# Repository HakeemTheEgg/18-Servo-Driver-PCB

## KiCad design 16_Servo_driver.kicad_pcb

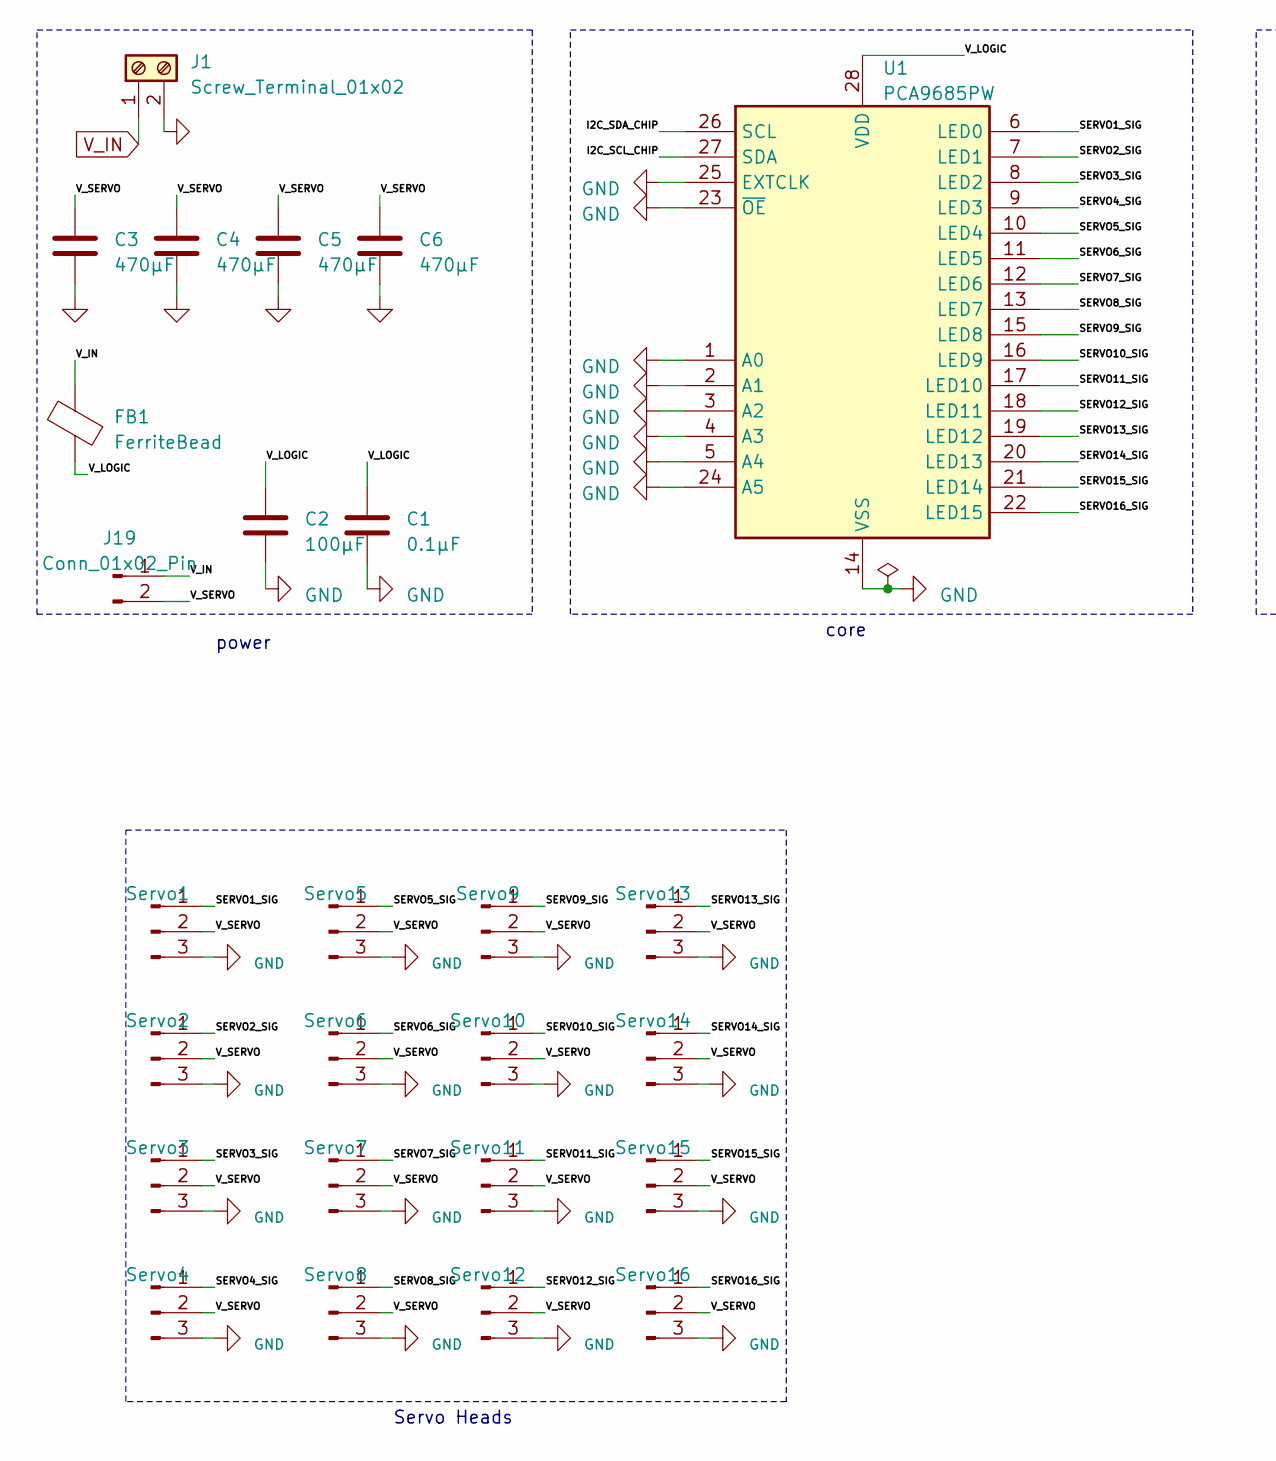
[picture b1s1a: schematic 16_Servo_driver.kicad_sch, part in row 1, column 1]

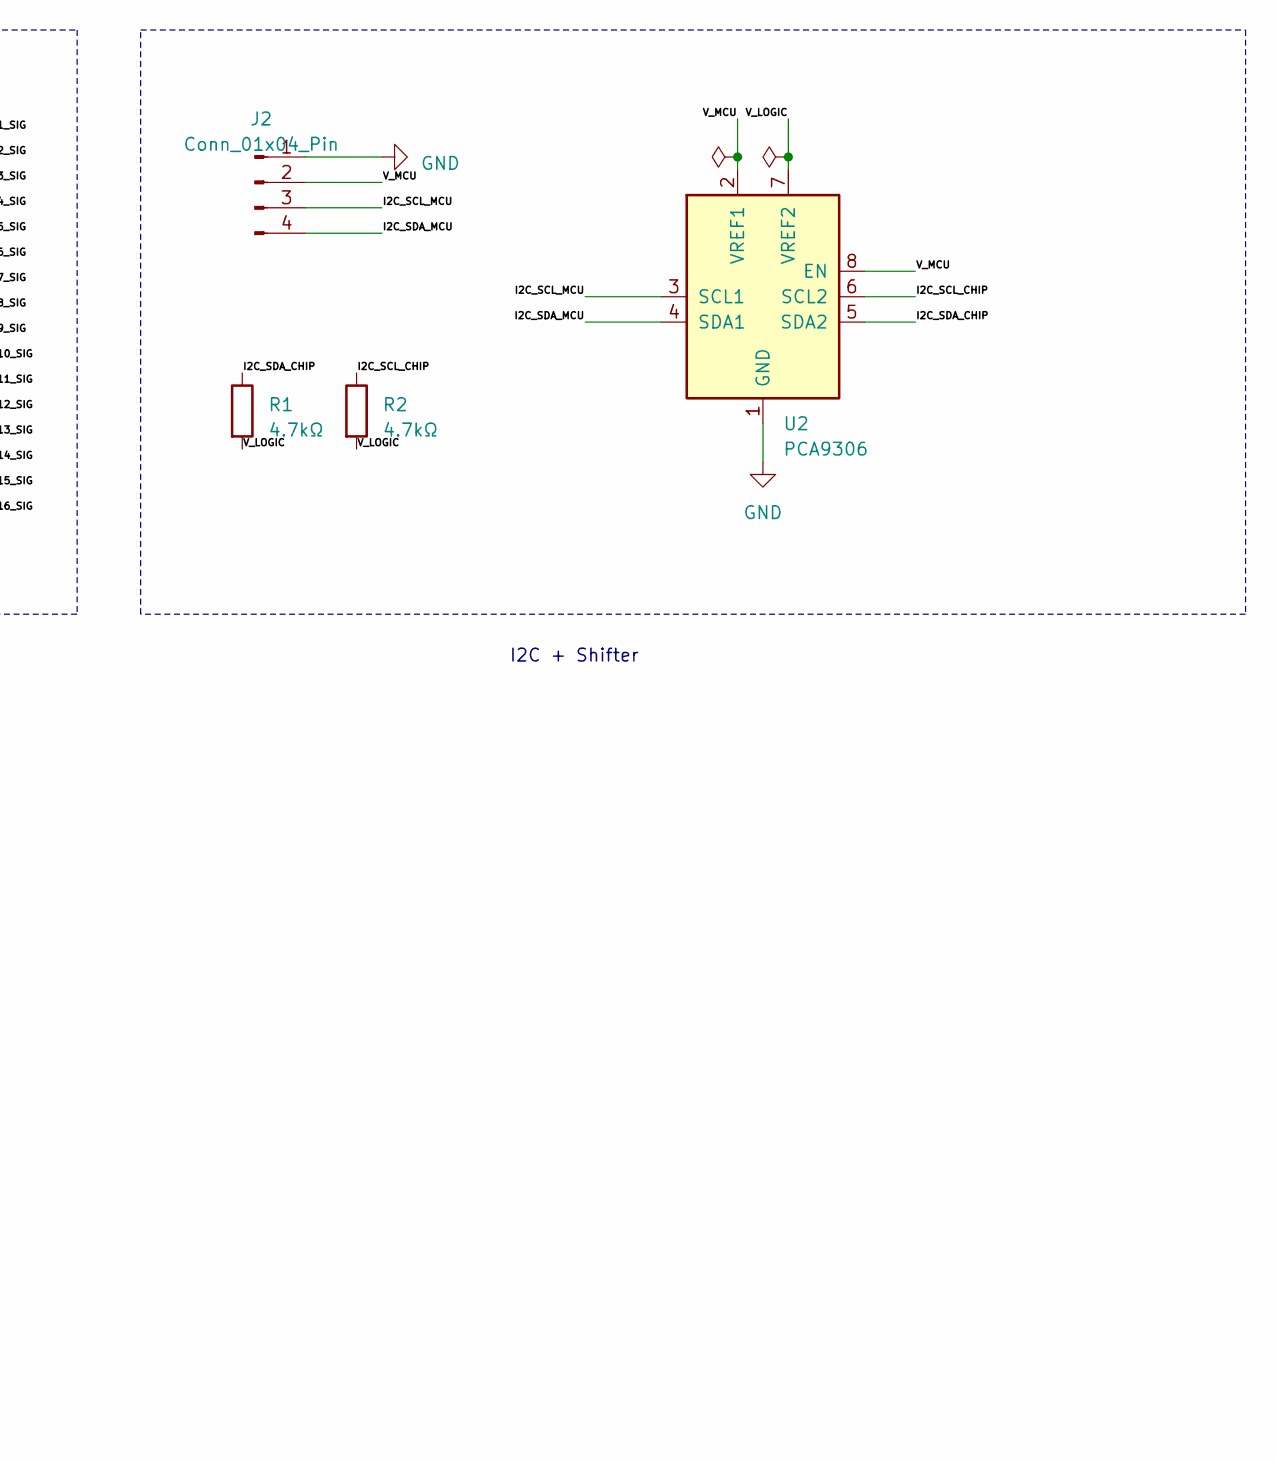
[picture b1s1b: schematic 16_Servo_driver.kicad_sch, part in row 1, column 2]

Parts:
C1: 0.1µF; C_0603_1608Metric
C2: 100µF; C_Radial_D8.0mm_H7.0mm_P3.50mm
C3, C4, C5, C6: 470µF; C_Radial_D8.0mm_H7.0mm_P3.50mm
FB1: FerriteBead; L_0805_2012Metric
J1: Screw_Terminal_01x02; TerminalBlock_Phoenix_MKDS-1,5-2-5.08_1x02_P5.08mm_Horizont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
J2: Conn_01x04_Pin; PinHeader_1x04_P2.54mm_Vertical
J19: Conn_01x02_Pin; PinHeader_1x02_P2.54mm_Vertical
R1, R2: 4.7kΩ; R_0603_1608Metric
Servo1, Servo2, Servo3, Servo4, Servo5, Servo6, Servo7, Servo8, Servo9, Servo10, Servo11, Servo12, Servo13, Servo14, Servo15, Servo16: Conn_01x03_Pin; PinHeader_1x03_P2.54mm_Vertical
U1: PCA9685PW; TSSOP-28_4.4x9.7mm_P0.65mm
U2: PCA9306; SSOP-8_2.95x2.8mm_P0.65mm

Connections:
/I2C_SCL_CHIP: R2.1, U1.27 (SDA), U2.6 (SCL2)
/I2C_SCL_MCU: J2.3, U2.3 (SCL1)
/I2C_SDA_CHIP: R1.1, U1.26 (SCL), U2.5 (SDA2)
/I2C_SDA_MCU: J2.4, U2.4 (SDA1)
/SERVO1_SIG: Servo1.1, U1.6 (LED0)
/SERVO2_SIG: Servo2.1, U1.7 (LED1)
/SERVO3_SIG: Servo3.1, U1.8 (LED2)
/SERVO4_SIG: Servo4.1, U1.9 (LED3)
/SERVO5_SIG: Servo5.1, U1.10 (LED4)
/SERVO6_SIG: Servo6.1, U1.11 (LED5)
/SERVO7_SIG: Servo7.1, U1.12 (LED6)
/SERVO8_SIG: Servo8.1, U1.13 (LED7)
/SERVO9_SIG: Servo9.1, U1.15 (LED8)
/SERVO10_SIG: Servo10.1, U1.16 (LED9)
/SERVO11_SIG: Servo11.1, U1.17 (LED10)
/SERVO12_SIG: Servo12.1, U1.18 (LED11)
/SERVO13_SIG: Servo13.1, U1.19 (LED12)
/SERVO14_SIG: Servo14.1, U1.20 (LED13)
/SERVO15_SIG: Servo15.1, U1.21 (LED14)
/SERVO16_SIG: Servo16.1, U1.22 (LED15)
/V_LOGIC: C1.1, C2.1, FB1.2, R1.2, R2.2, U1.28 (VDD), U2.7 (VREF2)
/V_MCU: J2.2, U2.2 (VREF1), U2.8 (EN)
/V_SERVO: C3.1, C4.1, C5.1, C6.1, J19.2, Servo1.2, Servo2.2, Servo3.2, Servo4.2, Servo5.2, Servo6.2, Servo7.2, Servo8.2, Servo9.2, Servo10.2, Servo11.2, Servo12.2, Servo13.2, Servo14.2, Servo15.2, Servo16.2
GND: C1.2, C2.2, C3.2, C4.2, C5.2, C6.2, J1.2, J2.1, Servo1.3, Servo2.3, Servo3.3, Servo4.3, Servo5.3, Servo6.3, Servo7.3, Servo8.3, Servo9.3, Servo10.3, Servo11.3, Servo12.3, Servo13.3, Servo14.3, Servo15.3, Servo16.3, U1.1 (A0), U1.2 (A1), U1.3 (A2), U1.4 (A3), U1.5 (A4), U1.14 (VSS), U1.23 (~OE), U1.24 (A5), U1.25 (EXTCLK), U2.1 (GND)
V_IN: FB1.1, J1.1, J19.1

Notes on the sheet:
I2C + Shifter
power
core
Servo Heads

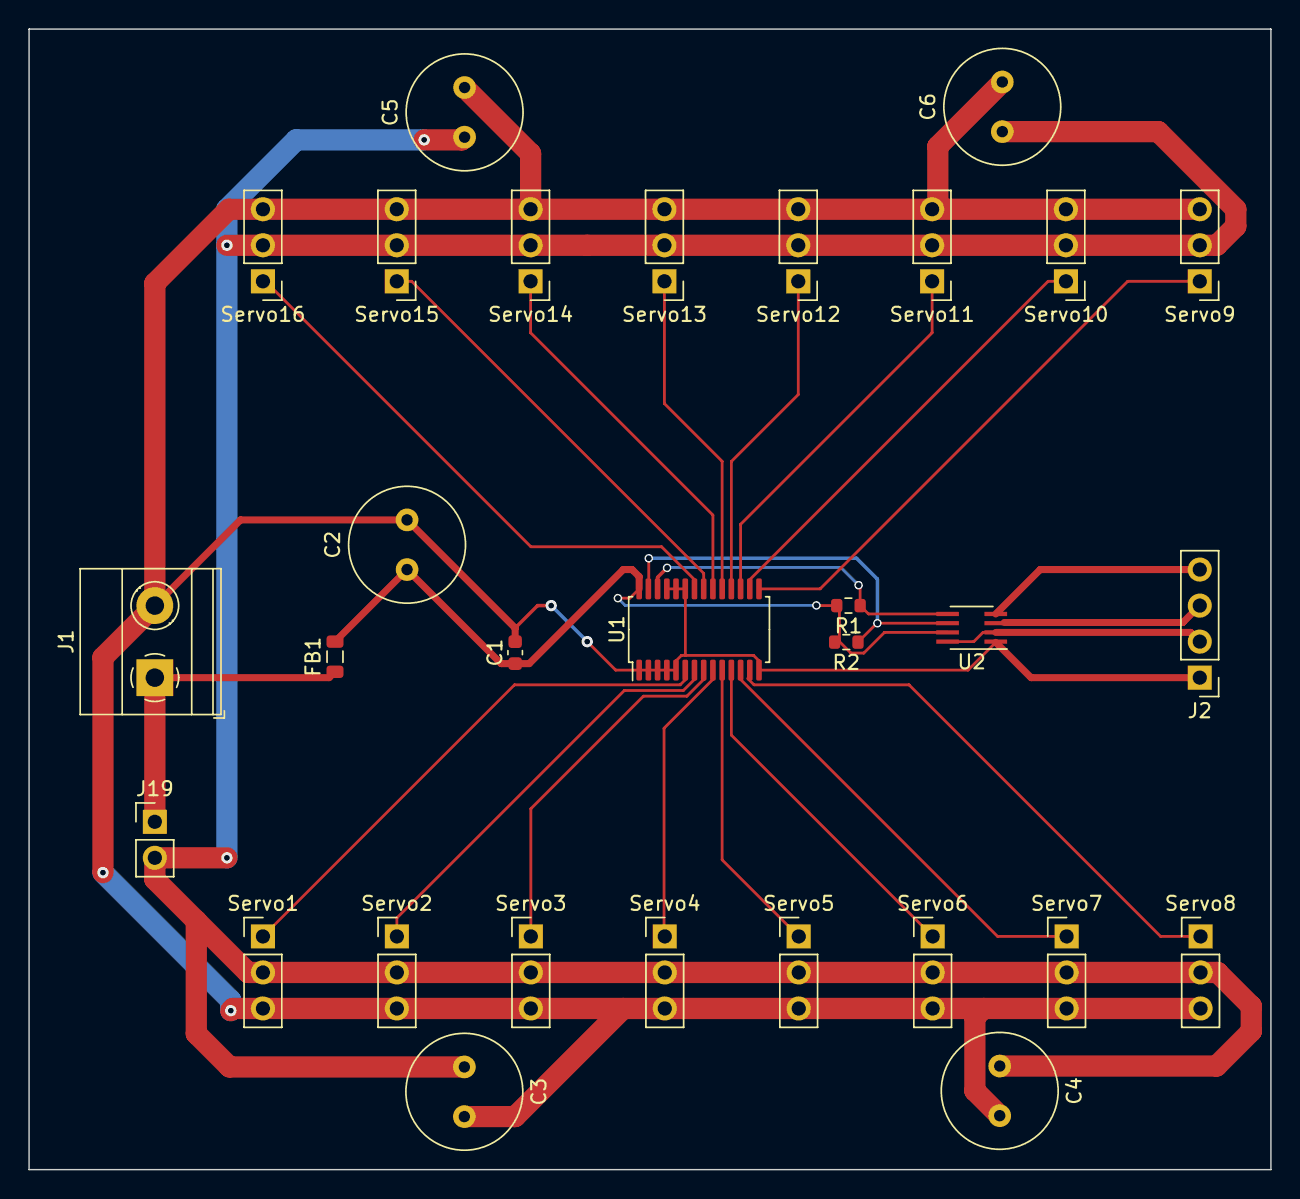
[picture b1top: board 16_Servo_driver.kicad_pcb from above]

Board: 2 copper layers, 87.5 x 80.4 mm, 30 parts (0 on the bottom side), 25 nets.
